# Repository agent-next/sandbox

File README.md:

# agent-next sandbox

Disposable cloud Linux sandboxes for your coding agent. Run long jobs,
untrusted code and heavy dependencies in the cloud instead of on your
machine, and share a public preview URL for anything that serves a port.

This repo holds three things that share one name, `sandbox`:

| piece | what it is | where |
| --- | --- | --- |
| Claude Code and Codex plugin | the sandbox MCP server plus the `sandbox` skill | [`plugins/sandbox`](plugins/sandbox) |
| `sbx` command-line tool | create, exec, list, kill from the shell | [`cli`](cli) |
| Cookbook | prompts to try with the plugin | [`cookbook`](cookbook) |

## Install the plugin

```bash
claude plugin marketplace add agent-next/sandbox
```

Then enable it and give it your API key:

```bash
claude plugin install sandbox@agent-next
export SBX_API_KEY=<your key>     # create one at https://sbx.agent-next.com/console
```

Start Claude Code from a shell where `SBX_API_KEY` is exported. Check with
`claude mcp list`: you should see the `sandbox` server.

Codex:

```bash
codex plugin marketplace add agent-next/sandbox
codex plugin add sandbox@agent-next
export SBX_API_KEY=<your key>     # Codex sends it as a bearer token
```

## Install the CLI

```bash
pip install "git+https://github.com/agent-next/sandbox#subdirectory=cli"
```

## Quickstart: create, exec, kill

There is no `sbx login`: the key comes only from the environment. Agents
and CI have no browser for the console — load an existing key from your
secret store and export it.

```bash
export E2B_API_KEY=<your key>     # SBX_API_KEY also works

id=$(sbx create)                  # a fresh sandbox; prints its id
sbx exec "$id" 'echo hello'       # prints: hello
sbx kill "$id"                    # always kill what you create
```

`sbx exec` passes stdout and stderr through and exits with the command's own
exit code. `sbx create --timeout-min N` sets an idle keep-alive (default
5 minutes); activity restarts the clock. The CLI opts into deletion at idle
expiry, so copy durable results out. CPU sandboxes created by the MCP plugin
instead pause at idle expiry and resume on the next exec or files call.

The same three steps from your agent: the plugin's tools are
`sandbox_create`, `sandbox_exec` and `sandbox_kill`, and the `sandbox` skill
tells the agent when to use them and to kill what it creates.

GPU from the shell: `sbx gpu create --vram 4`, then `sbx gpu exec ID -c '...'`,
`pause`, `resume` and `kill` (see [cli/README.md](cli/README.md#gpu-leases)).
For CUDA work, also try the [1 GiB small-GPU quickstart](cookbook/small-gpu/README.md).
It includes a Python client that checks a tiny GPU computation and destroys
the lease. GPU-enabled keys and available capacity are required. This MIT
repository contains the client kit; the hosted service's backend is separate.

## Development

Start with [AGENTS.md](AGENTS.md) for the check commands and acceptance rules.
CLI setup and usage are in [cli/README.md](cli/README.md). The release process
is in [RELEASING.md](RELEASING.md).

[nightly-smoke.yml](.github/workflows/nightly-smoke.yml) runs `scripts/release_smoke.py`
against the latest tag each night and uploads its JSON receipt. Set the `SBX_SMOKE_KEY`
secret for live checks. Missing credentials fail the nightly gate and leave a JSON
receipt; scheduled failures file a "nightly smoke failed" issue auto-closed after
a successful live run.

## License

MIT — see [LICENSE](LICENSE).

## Security

See [SECURITY.md](SECURITY.md).

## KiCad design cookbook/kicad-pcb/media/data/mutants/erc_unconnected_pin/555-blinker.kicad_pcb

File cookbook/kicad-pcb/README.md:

# kicad-pcb — judge a small PCB design in a disposable sandbox

The agent designs a real 2-layer board — a 555 astable LED blinker —
in KiCad s-expression format, and a judge it cannot fool decides whether
the result is right. KiCad runs headless (`kicad-cli` 9.0.9, SHA256-pinned
official AppImage), and every gate is checked by an independent
stdlib-Python oracle (`judge/oracle.py`) that parses the reports and the
exported Gerber/Excellon files itself — "the tool ran" is never the pass
criterion.

A disposable sandbox helps because KiCad is a heavy GUI toolchain: the
judge installs a verified 200 MB AppImage, runs ERC/DRC/gerber/drill
exports, and throws it all away. Nothing touches the host or the repo.

## Ask your agent

> In a fresh sandbox, clone this repo and go to `cookbook/kicad-pcb/`.
> Run `bash judge/setup.sh`, then look at `SPEC.md`. Design (or fix) a
> small 2-layer KiCad project — a 555 astable LED blinker, board
> <= 50 x 50 mm — as `examples/good/555-blinker/` (`.kicad_pro`,
> `.kicad_sch`, `.kicad_pcb`). Iterate with
> `bash judge/grade.sh examples/good/555-blinker --json /tmp/v.json`
> until `overall_pass` is `true`. The judge is in `judge/`; do not modify
> it. Finish with `bash judge/selftest.sh`.

## One-command run

```bash
python3 run.py            # clones --ref (default main) in a sandbox
python3 run.py --ref my-branch --keep
```

`run.py` creates an `sbx` sandbox, clones the repo, runs `setup.sh`,
`selftest.sh`, and `grade.sh`, prints the verdict JSON and per-step wall
times, then always kills the sandbox and verifies it is gone.

## What is checked (gates)

| gate | check | pass rule |
|---|---|---|
| G1 | `kicad-cli sch erc` JSON | 0 errors, and every warning type is in the allow-list (SPEC.md) |
| G2 | `kicad-cli pcb drc` JSON | 0 violations, 0 unconnected items — run with the judge's pinned rule severities, not the artifact's |
| G3 | schematic vs PCB netlists | per-net `(ref, pin)` == `(ref, pad)` membership, 0 unrouted, 555 + LED placed, same part references |
| G4 | Edge.Cuts parsed from `.kicad_pcb` | outline is a closed loop, no open segment ends |
| G5 | gerber export (7 layers) | >=1 aperture + >=1 draw/flash op per layer; Edge.Cuts extents match the board to 0.1 mm |
| G6 | Excellon drill export | every through-hole pad/via has a drill, a matching tool exists, hits cover all holes |
| G7 | `.kicad_pcb` + `.kicad_pro` | board <= 50x50 mm; netclass clearance/track >= 0.20 mm, via drill >= 0.30 mm; every copper track >= 0.20 mm |

## Measured wall time (this sandbox, 2 vCPU / 4 GB)

Two cold runs on different days; network speed dominates `setup.sh`.

| step | time |
|---|---|
| `judge/setup.sh` (cold, downloads 208 MB) | 18-34 s |
| `judge/selftest.sh` (good x2 + unit tests + 11 mutants) | 60-120 s |
| `judge/grade.sh` on the good example | 3-6 s |

## Rebuilding the media

`media/make_media.sh` needs `judge/setup.sh` run first (kicad-cli renders
the board), the judge outputs from `bash media/make_data.sh`, and `ffmpeg`
plus `ffprobe` on PATH. Python deps install hash-pinned into
`media/.venv`. Then `bash media/make_media.sh` rewrites `result.png`,
`loop.png`, `demo.mp4` and `MANIFEST.json`.

See `RECEIPT.md` for pasted output and `REPRODUCE.md` for independent
reproduction.

## Layout

```
SPEC.md                   contract: gates, oracle, tolerances
judge/setup.sh            pinned KiCad 9.0.9 install (sha256-checked)
judge/VERSIONS.txt        what setup.sh installed (tool --version output)
judge/requirements.txt    hash-pinned pip deps (media only; judge is stdlib)
judge/grade.sh            runs kicad-cli + oracle, emits verdict JSON
judge/oracle.py           stdlib-only independent checker
judge/test_oracle.py      oracle unit tests (in-memory fixtures)
judge/selftest.sh         determinism + unit tests + mutant kill-rate (>= 90%)
judge/mutants.py          11 single-edit mutants of the good project
examples/good/555-blinker/  known-good project (~83 KB, self-contained)
tools/                    generators that produced the example
media/                    result.png, loop.png, demo.mp4, make_media.sh
run.py                    one-command sandbox run
```

## Limits

- ERC/DRC check the *files'* rules. The good board reports 19 ERC
  warnings, all `lib_symbol_issues` — inherent to a self-contained
  artifact (symbols embedded, no library table) graded headless; the G1
  gate fails on every other warning type (see SPEC.md's allow-list).
- The judge does not simulate the circuit (no timing/frequency check).
- Gerber/drill parsing is deliberately shallow: it verifies real
  geometry exists on every exported layer, not fabrication readiness.
- `run.py` requires the `sbx` CLI and `SBX_API_KEY`/`E2B_API_KEY`.

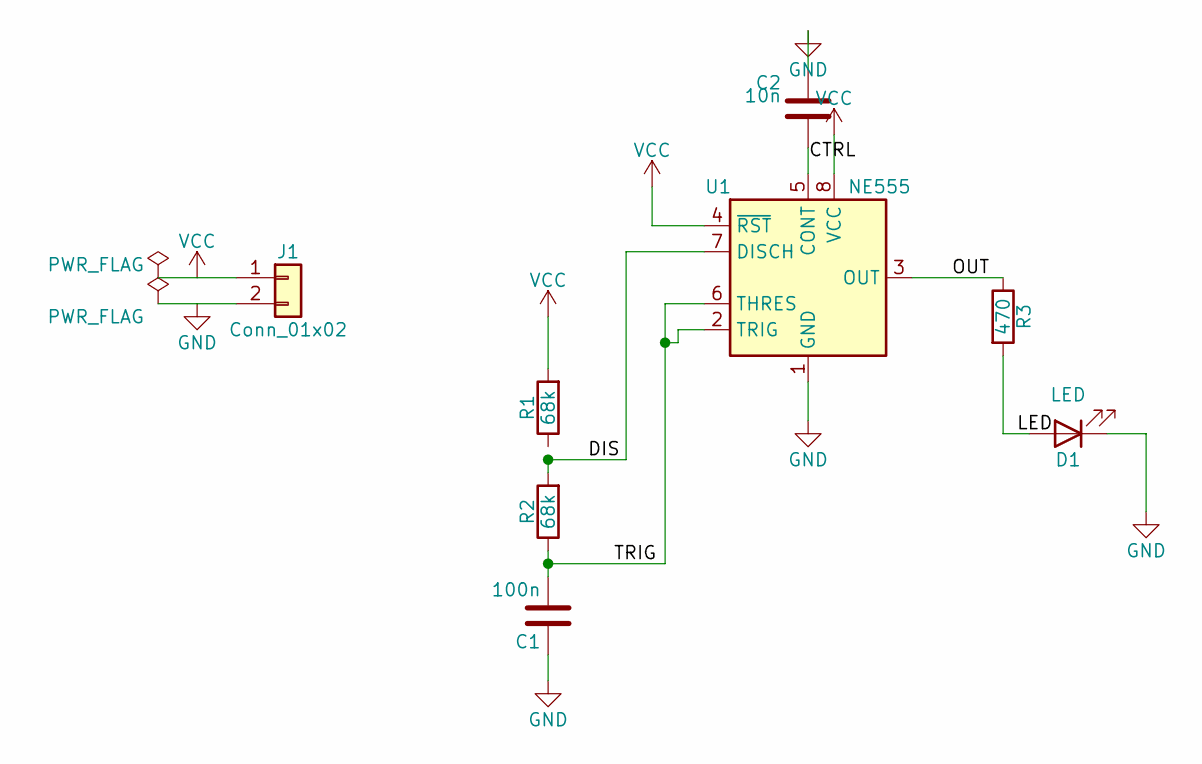
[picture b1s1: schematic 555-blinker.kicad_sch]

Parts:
C1: 100n; C_0805_2012Metric
C2: 10n; C_0805_2012Metric
D1: LED; LED_0805_2012Metric
J1: Conn_01x02; PinHeader_1x02_P2.54mm_Vertical
R1, R2: 68k; R_0805_2012Metric
R3: 470; R_0805_2012Metric
U1: NE555; SOIC-8_3.9x4.9mm_P1.27mm

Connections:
CTRL: C2.2, U1.5 (CONT)
DIS: R1.1, R2.2, U1.7 (DISCH)
GND: C1.1, C2.1, D1.1 (K), J1.2, U1.1 (GND)
LED: D1.2 (A), R3.2
OUT: R3.1, U1.3 (OUT)
TRIG: C1.2, R2.1, U1.2 (TRIG), U1.6 (THRES)
VCC: J1.1, R1.2, U1.4 (~RST), U1.8 (VCC)

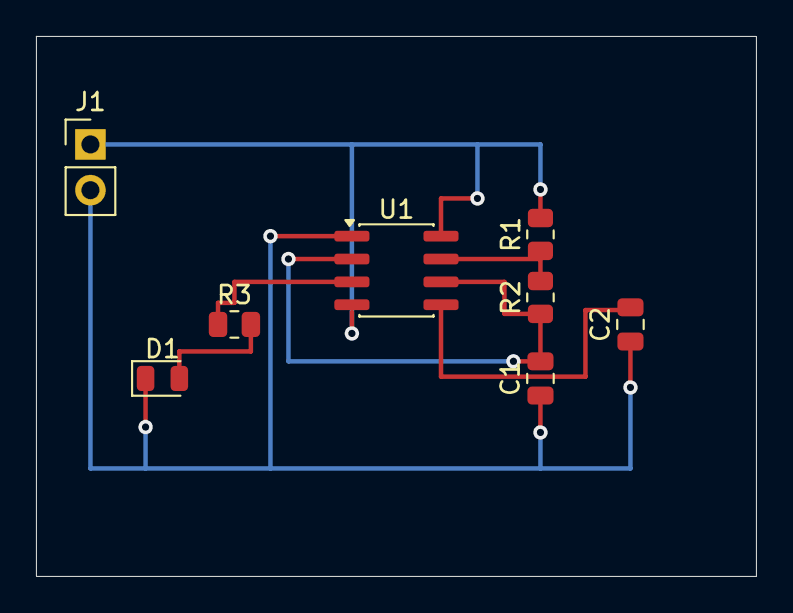
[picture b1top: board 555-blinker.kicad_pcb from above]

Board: 2 copper layers, 40.0 x 30.0 mm, 8 parts (0 on the bottom side), 7 nets.
